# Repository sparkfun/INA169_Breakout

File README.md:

SparkFun INA169 Current Sensing Breakout
===============

[  
*INA169 Current Sense Breakout Board (SEN-12040)*](https://www.sparkfun.com/products/12040)

High-side current sense breakout board. [The datasheet can be found here.](http://www.ti.com/lit/ds/symlink/ina169.pdf)

This part was created in Eagle v6.0.0. Example sketches were created in Arduino v1.0.5.

Repository Contents
-------------------

* **/Firmware** - Example Arduino sketches
* **/Hardware** - All Eagle design files (.brd, .sch, .STL)
* **/Production** - Test bed files and production panel files

Documentation
-------------------
* **[Hookup Guide](https://learn.sparkfun.com/tutorials/ina169-breakout-board-hookup-guide)**

Version History
---------------
* **v1.0** Initial release

License Information
-------------------
The hardware is released under [Creative Commons Share-alike 3.0](http://creativecommons.org/licenses/by-sa/3.0/).  
All other code is open source so please feel free to do anything you want with it; you buy me a beer if you use this and we meet someday ([Beerware license](http://en.wikipedia.org/wiki/Beerware)).

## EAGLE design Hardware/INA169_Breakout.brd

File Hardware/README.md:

# What Are these Files?

The .sch and .brd files hare are Eagle CAD schematic and PCB design files.

These files were created with Eagle 6.0.0, you'll need Eagle 6.0 or later to open them up. There is a free, lite, version of Eagle available from [cadsoftusa.com](cadsoftusa.com).

# License

This product is open source! These Eagle files are released under the Creative Commons Share-Alike Attribution license ([CC BY-SA 3.0](http://creativecommons.org/licenses/by-sa/3.0/us/)).

Please use, reuse, and modify these files as you see fit. Please maintain attribution and release anything derivative under the same license.

- Your friends at SparkFun.

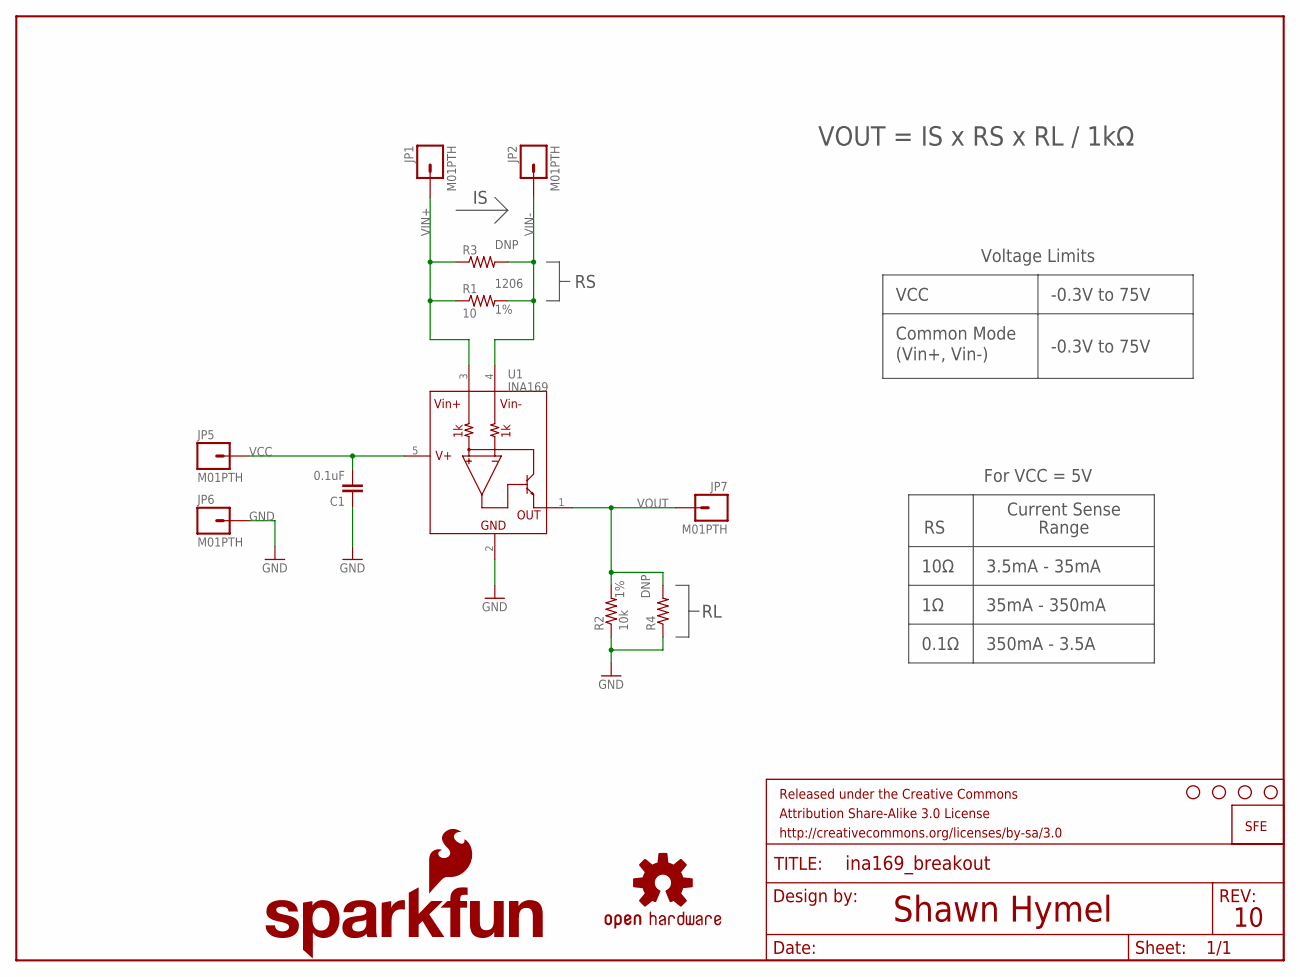
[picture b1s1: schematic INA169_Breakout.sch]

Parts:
C1: 0.1uF; 0603-CAP
FRAME1: FRAME-LETTER; CREATIVE_COMMONS
JP1, JP2, JP5, JP6, JP7: M01PTH; 1X01
LOGO1: SFE_LOGO_NAME_FLAME.1_INCH; SFE_LOGO_NAME_FLAME_.1
LOGO2: OSHW-LOGOS; OSHW-LOGO-S
LOGO3: LOGO-SFESK; SFE-LOGO-FLAME
R1: 10; 1206
R2: 10k; 0603-RES
R3: RESISTORPTH-2W; AXIAL-0.8
R4: RESISTORPTH-1/4W; AXIAL-0.4
STANDOFF1, STANDOFF2, STANDOFF3, STANDOFF4: STAND-OFF
U1: INA169; SOT23-5

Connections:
GND: C1.1, JP6.1, R2.1, R4.P$1 (1), U1.2 (GND)
VCC: C1.2, JP5.1, U1.5 (V+)
VIN+: JP1.1, R1.1, R3.P$1 (1), U1.3 (VIN+)
VIN-: JP2.1, R1.2, R3.P$2 (2), U1.4 (VIN-)
VOUT: JP7.1, R2.2, R4.P$2 (2), U1.1 (OUT)

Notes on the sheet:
Shawn Hymel
For VCC = 5V
Range
Current Sense
10Ω
0.1Ω
3.5mA - 35mA
35mA - 350mA
350mA - 3.5A
Voltage Limits
VCC
Common Mode
(Vin+, Vin-)
-0.3V to 75V
VOUT = IS x RS x RL / 1kΩ

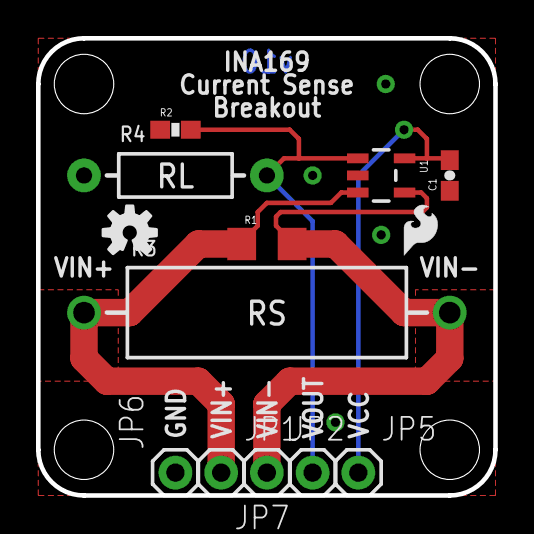
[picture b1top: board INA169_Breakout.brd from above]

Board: 2 copper layers, 25.4 x 25.4 mm, 19 parts (1 on the bottom side), 5 nets.

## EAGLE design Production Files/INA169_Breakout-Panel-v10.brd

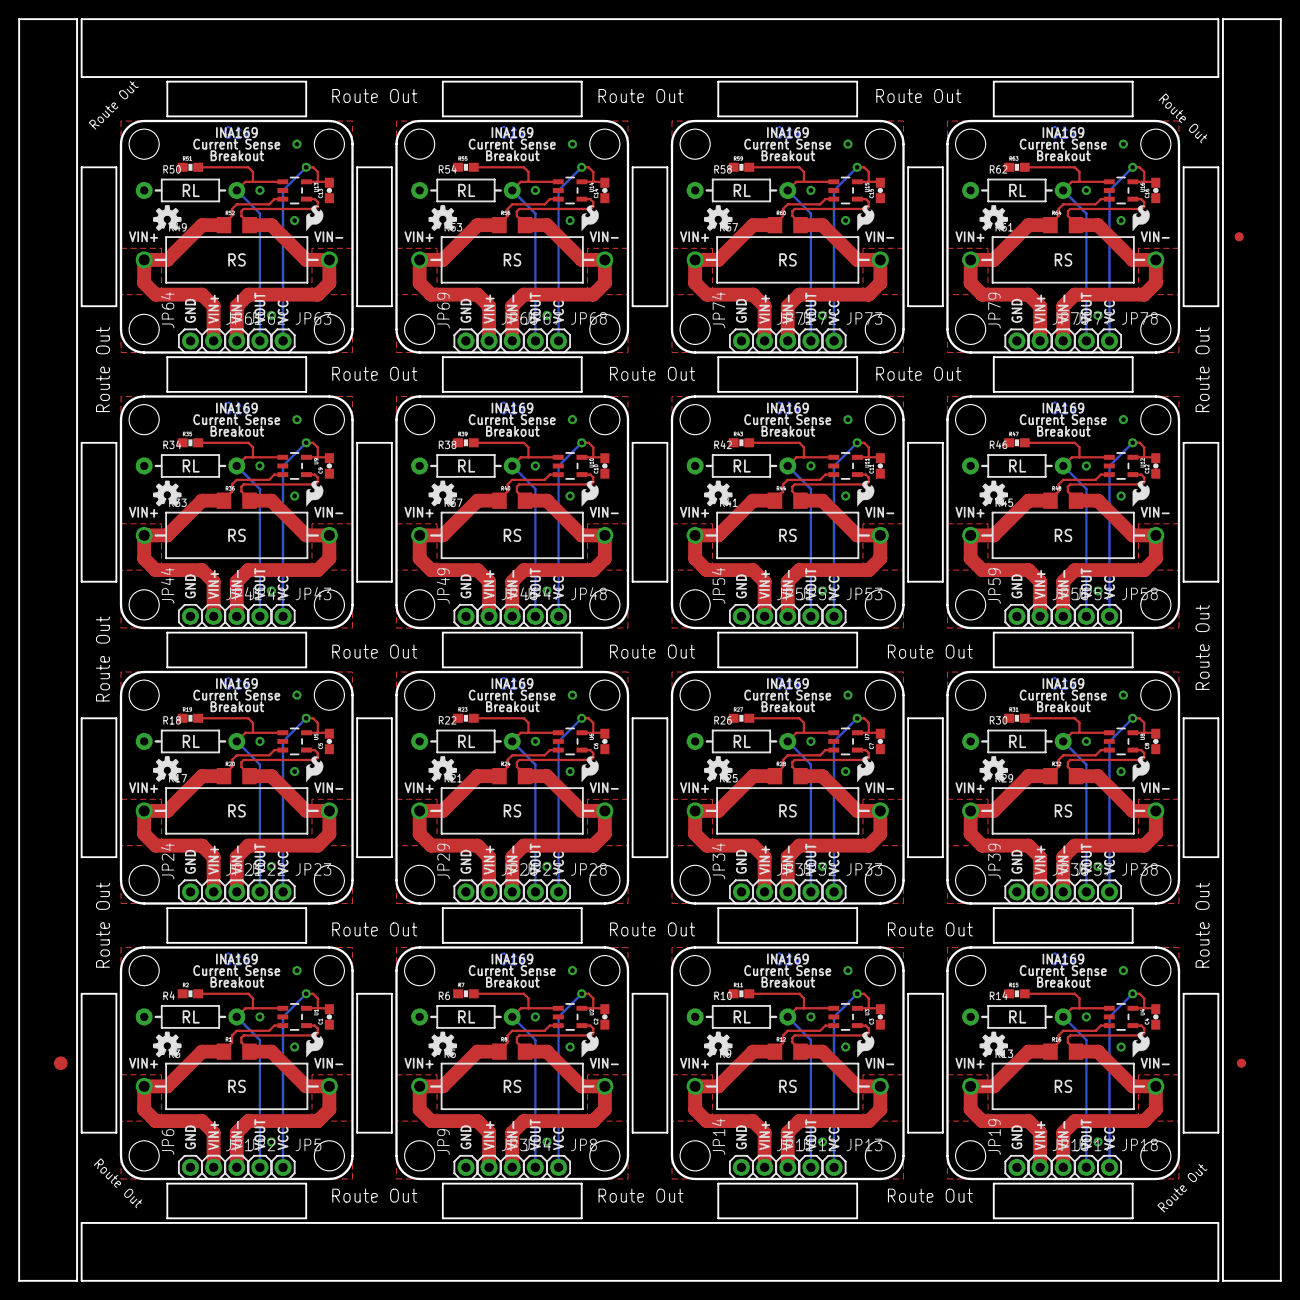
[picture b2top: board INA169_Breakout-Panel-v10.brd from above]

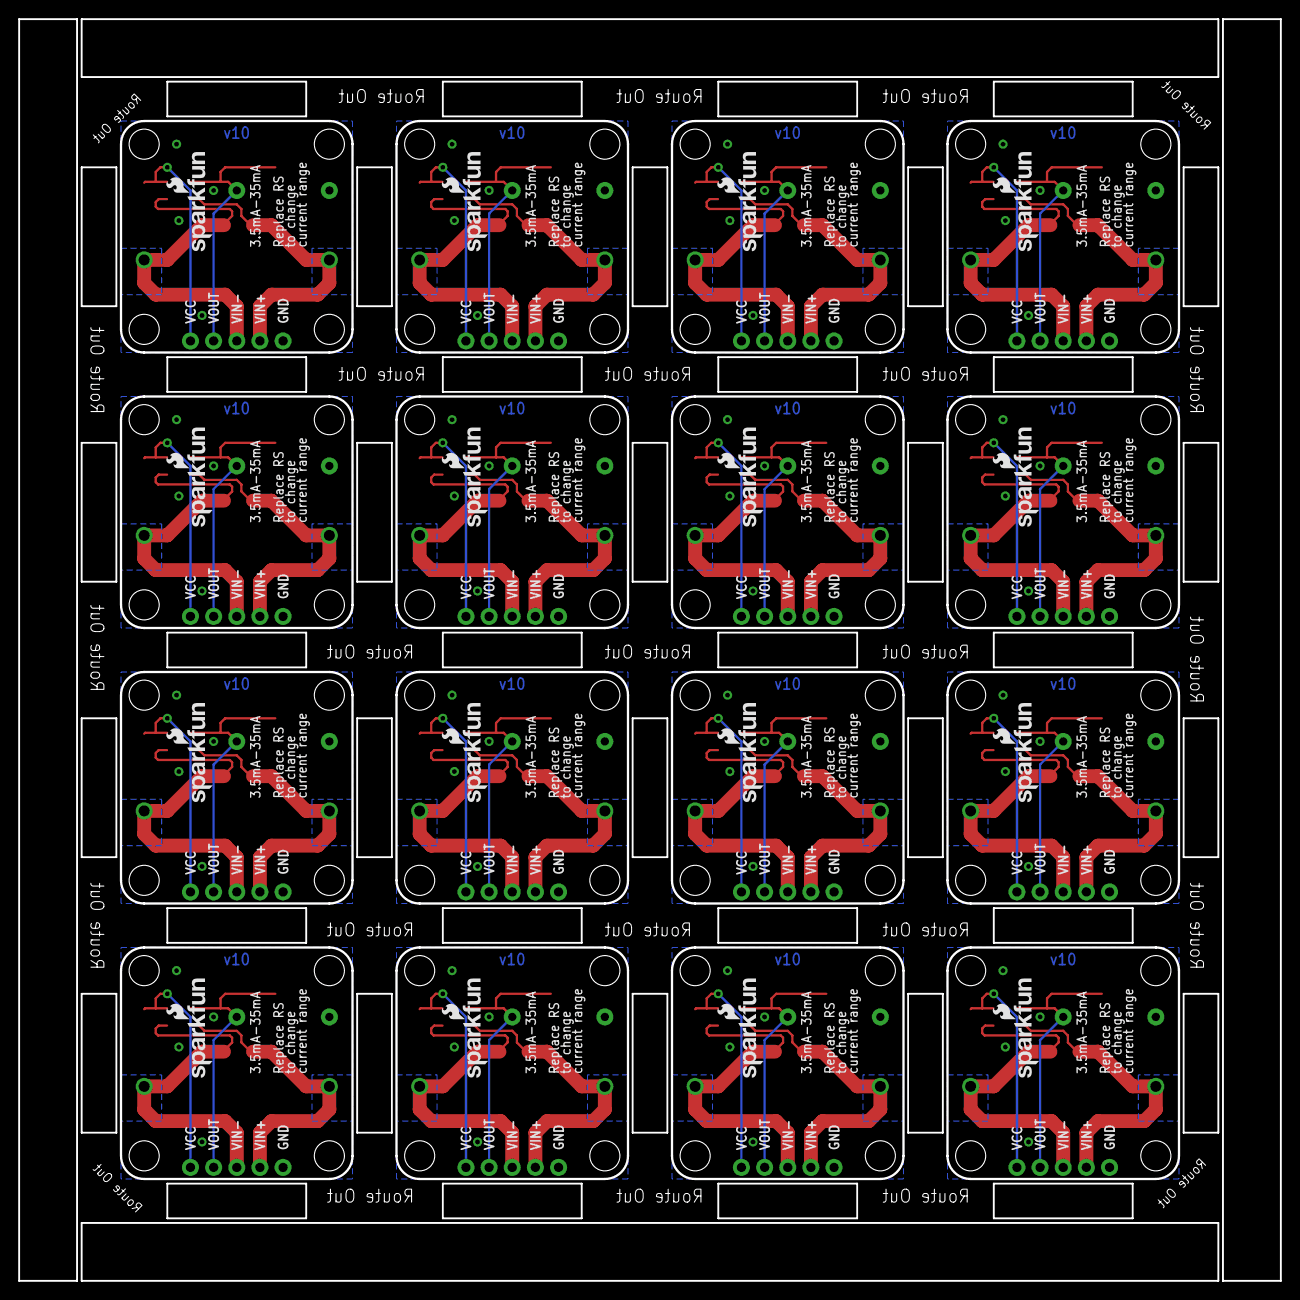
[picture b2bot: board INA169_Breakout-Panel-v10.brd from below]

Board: 2 copper layers, 138.4 x 138.4 mm, 291 parts (16 on the bottom side), 80 nets.

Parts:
C1, C2, C3, C4, C5, C6, C7, C8, C9, C10, C11, C12, C13, C14, C15, C16: 0.1uF; 0603-CAP
E$1: FIDUCIAL-1.5X3
E$4, E$5: FIDUCIAL-1X2
JP1, JP2, JP3, JP4, JP5, JP6, JP7, JP8, JP9, JP10, JP11, JP12, JP13, JP14, JP15, JP16, JP17, JP18, JP19, JP20, JP21, JP22, JP23, JP24, JP25, JP26, JP27, JP28, JP29, JP30, JP31, JP32, JP33, JP34, JP35, JP36, JP37, JP38, JP39, JP40, JP41, JP42, JP43, JP44, JP45, JP46, JP47, JP48, JP49, JP50, JP51, JP52, JP53, JP54, JP55, JP56, JP57, JP58, JP59, JP60, JP61, JP62, JP63, JP64, JP65, JP66, JP67, JP68, JP69, JP70, JP71, JP72, JP73, JP74, JP75, JP76, JP77, JP78, JP79, JP80: M01PTH; 1X01
LOGO1, LOGO4, LOGO7, LOGO10, LOGO13, LOGO16, LOGO19, LOGO22, LOGO25, LOGO28, LOGO31, LOGO34, LOGO37, LOGO40, LOGO43, LOGO46: SFE_LOGO_NAME_FLAME.1_INCH; SFE_LOGO_NAME_FLAME_.1
LOGO2, LOGO5, LOGO8, LOGO11, LOGO14, LOGO17, LOGO20, LOGO23, LOGO26, LOGO29, LOGO32, LOGO35, LOGO38, LOGO41, LOGO44, LOGO47: OSHW-LOGOS; OSHW-LOGO-S
LOGO3, LOGO6, LOGO9, LOGO12, LOGO15, LOGO18, LOGO21, LOGO24, LOGO27, LOGO30, LOGO33, LOGO36, LOGO39, LOGO42, LOGO45, LOGO48: LOGO-SFESK; SFE-LOGO-FLAME
R1, R8, R12, R16, R20, R24, R28, R32, R36, R40, R44, R48, R52, R56, R60, R64: 10; 1206
R2, R7, R11, R15, R19, R23, R27, R31, R35, R39, R43, R47, R51, R55, R59, R63: 10k; 0603-RES
R3, R5, R9, R13, R17, R21, R25, R29, R33, R37, R41, R45, R49, R53, R57, R61: AXIAL-0.8
R4, R6, R10, R14, R18, R22, R26, R30, R34, R38, R42, R46, R50, R54, R58, R62: AXIAL-0.4
STANDOFF1, STANDOFF2, STANDOFF3, STANDOFF4, STANDOFF5, STANDOFF6, STANDOFF7, STANDOFF8, STANDOFF9, STANDOFF10, STANDOFF11, STANDOFF12, STANDOFF13, STANDOFF14, STANDOFF15, STANDOFF16, STANDOFF17, STANDOFF18, STANDOFF19, STANDOFF20, STANDOFF21, STANDOFF22, STANDOFF23, STANDOFF24, STANDOFF25, STANDOFF26, STANDOFF27, STANDOFF28, STANDOFF29, STANDOFF30, STANDOFF31, STANDOFF32, STANDOFF33, STANDOFF34, STANDOFF35, STANDOFF36, STANDOFF37, STANDOFF38, STANDOFF39, STANDOFF40, STANDOFF41, STANDOFF42, STANDOFF43, STANDOFF44, STANDOFF45, STANDOFF46, STANDOFF47, STANDOFF48, STANDOFF49, STANDOFF50, STANDOFF51, STANDOFF52, STANDOFF53, STANDOFF54, STANDOFF55, STANDOFF56, STANDOFF57, STANDOFF58, STANDOFF59, STANDOFF60, STANDOFF61, STANDOFF62, STANDOFF63, STANDOFF64: STAND-OFF
U1, U2, U3, U4, U5, U6, U7, U8, U9, U10, U11, U12, U13, U14, U15, U16: INA169; SOT23-5

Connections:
GND: C1.1, JP6.1, R2.1, R4.P$1, U1.2
GND1: C2.1, JP9.1, R6.P$1, R7.1, U2.2
GND2: C3.1, JP14.1, R10.P$1, R11.1, U3.2
GND3: C4.1, JP19.1, R14.P$1, R15.1, U4.2
GND4: C5.1, JP24.1, R18.P$1, R19.1, U5.2
GND5: C6.1, JP29.1, R22.P$1, R23.1, U6.2
GND6: C7.1, JP34.1, R26.P$1, R27.1, U7.2
GND7: C8.1, JP39.1, R30.P$1, R31.1, U8.2
GND8: C9.1, JP44.1, R34.P$1, R35.1, U9.2
GND9: C10.1, JP49.1, R38.P$1, R39.1, U10.2
GND10: C11.1, JP54.1, R42.P$1, R43.1, U11.2
GND11: C12.1, JP59.1, R46.P$1, R47.1, U12.2
GND12: C13.1, JP64.1, R50.P$1, R51.1, U13.2
GND13: C14.1, JP69.1, R54.P$1, R55.1, U14.2
GND14: C15.1, JP74.1, R58.P$1, R59.1, U15.2
GND15: C16.1, JP79.1, R62.P$1, R63.1, U16.2
VCC: C1.2, JP5.1, U1.5
VCC1: C2.2, JP8.1, U2.5
VCC2: C3.2, JP13.1, U3.5
VCC3: C4.2, JP18.1, U4.5
VCC4: C5.2, JP23.1, U5.5
VCC5: C6.2, JP28.1, U6.5
VCC6: C7.2, JP33.1, U7.5
VCC7: C8.2, JP38.1, U8.5
VCC8: C9.2, JP43.1, U9.5
VCC9: C10.2, JP48.1, U10.5
VCC10: C11.2, JP53.1, U11.5
VCC11: C12.2, JP58.1, U12.5
VCC12: C13.2, JP63.1, U13.5
VCC13: C14.2, JP68.1, U14.5
VCC14: C15.2, JP73.1, U15.5
VCC15: C16.2, JP78.1, U16.5
VIN+: JP1.1, R1.1, R3.P$1, U1.3
VIN+1: JP3.1, R5.P$1, R8.1, U2.3
VIN+2: JP11.1, R9.P$1, R12.1, U3.3
VIN+3: JP16.1, R13.P$1, R16.1, U4.3
VIN+4: JP21.1, R17.P$1, R20.1, U5.3
VIN+5: JP26.1, R21.P$1, R24.1, U6.3
VIN+6: JP31.1, R25.P$1, R28.1, U7.3
VIN+7: JP36.1, R29.P$1, R32.1, U8.3
VIN+8: JP41.1, R33.P$1, R36.1, U9.3
VIN+9: JP46.1, R37.P$1, R40.1, U10.3
VIN+10: JP51.1, R41.P$1, R44.1, U11.3
VIN+11: JP56.1, R45.P$1, R48.1, U12.3
VIN+12: JP61.1, R49.P$1, R52.1, U13.3
VIN+13: JP66.1, R53.P$1, R56.1, U14.3
VIN+14: JP71.1, R57.P$1, R60.1, U15.3
VIN+15: JP76.1, R61.P$1, R64.1, U16.3
VIN-: JP2.1, R1.2, R3.P$2, U1.4
VIN-1: JP4.1, R5.P$2, R8.2, U2.4
VIN-2: JP12.1, R9.P$2, R12.2, U3.4
VIN-3: JP17.1, R13.P$2, R16.2, U4.4
VIN-4: JP22.1, R17.P$2, R20.2, U5.4
VIN-5: JP27.1, R21.P$2, R24.2, U6.4
VIN-6: JP32.1, R25.P$2, R28.2, U7.4
VIN-7: JP37.1, R29.P$2, R32.2, U8.4
VIN-8: JP42.1, R33.P$2, R36.2, U9.4
VIN-9: JP47.1, R37.P$2, R40.2, U10.4
VIN-10: JP52.1, R41.P$2, R44.2, U11.4
VIN-11: JP57.1, R45.P$2, R48.2, U12.4
VIN-12: JP62.1, R49.P$2, R52.2, U13.4
VIN-13: JP67.1, R53.P$2, R56.2, U14.4
VIN-14: JP72.1, R57.P$2, R60.2, U15.4
VIN-15: JP77.1, R61.P$2, R64.2, U16.4
VOUT: JP7.1, R2.2, R4.P$2, U1.1
VOUT1: JP10.1, R6.P$2, R7.2, U2.1
VOUT2: JP15.1, R10.P$2, R11.2, U3.1
VOUT3: JP20.1, R14.P$2, R15.2, U4.1
VOUT4: JP25.1, R18.P$2, R19.2, U5.1
VOUT5: JP30.1, R22.P$2, R23.2, U6.1
VOUT6: JP35.1, R26.P$2, R27.2, U7.1
VOUT7: JP40.1, R30.P$2, R31.2, U8.1
VOUT8: JP45.1, R34.P$2, R35.2, U9.1
VOUT9: JP50.1, R38.P$2, R39.2, U10.1
VOUT10: JP55.1, R42.P$2, R43.2, U11.1
VOUT11: JP60.1, R46.P$2, R47.2, U12.1
VOUT12: JP65.1, R50.P$2, R51.2, U13.1
VOUT13: JP70.1, R54.P$2, R55.2, U14.1
VOUT14: JP75.1, R58.P$2, R59.2, U15.1
VOUT15: JP80.1, R62.P$2, R63.2, U16.1

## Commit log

2013-08-16 Created initial folder structure
2013-08-20 Added prototype board files for review
2013-08-27 Fixed changes from board review. Ready for prototype.
2013-10-01 Fixed silkscreen. Ready for review.
2013-10-16 Added tables on sch, added pads on brd
2013-10-16 Changed to smaller SFE logo on brd
2013-10-21 Created Panel
2013-11-11 Fixed readme
2013-11-13 Added Arduino example to Firmware
2013-11-13 Updated README with Production Files info
2013-11-13 Updated comments in example code
2013-11-14 Updated READMEs, added Fritzing part, corrected comments in example sketch
2014-01-07 Re-printed pdf version of schematic
2025-02-19 Add Board Dimensions
2025-06-27 Update README.md
    Updating link

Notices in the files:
parts and their libraries:
SparkFun-Aesthetics: Licensing: CC v3.0 Share-Alike You are welcome to use this library for commercial purposes.
SparkFun-Aesthetics: Released under the Creative Commons Attribution Share-Alike 3.0 License
